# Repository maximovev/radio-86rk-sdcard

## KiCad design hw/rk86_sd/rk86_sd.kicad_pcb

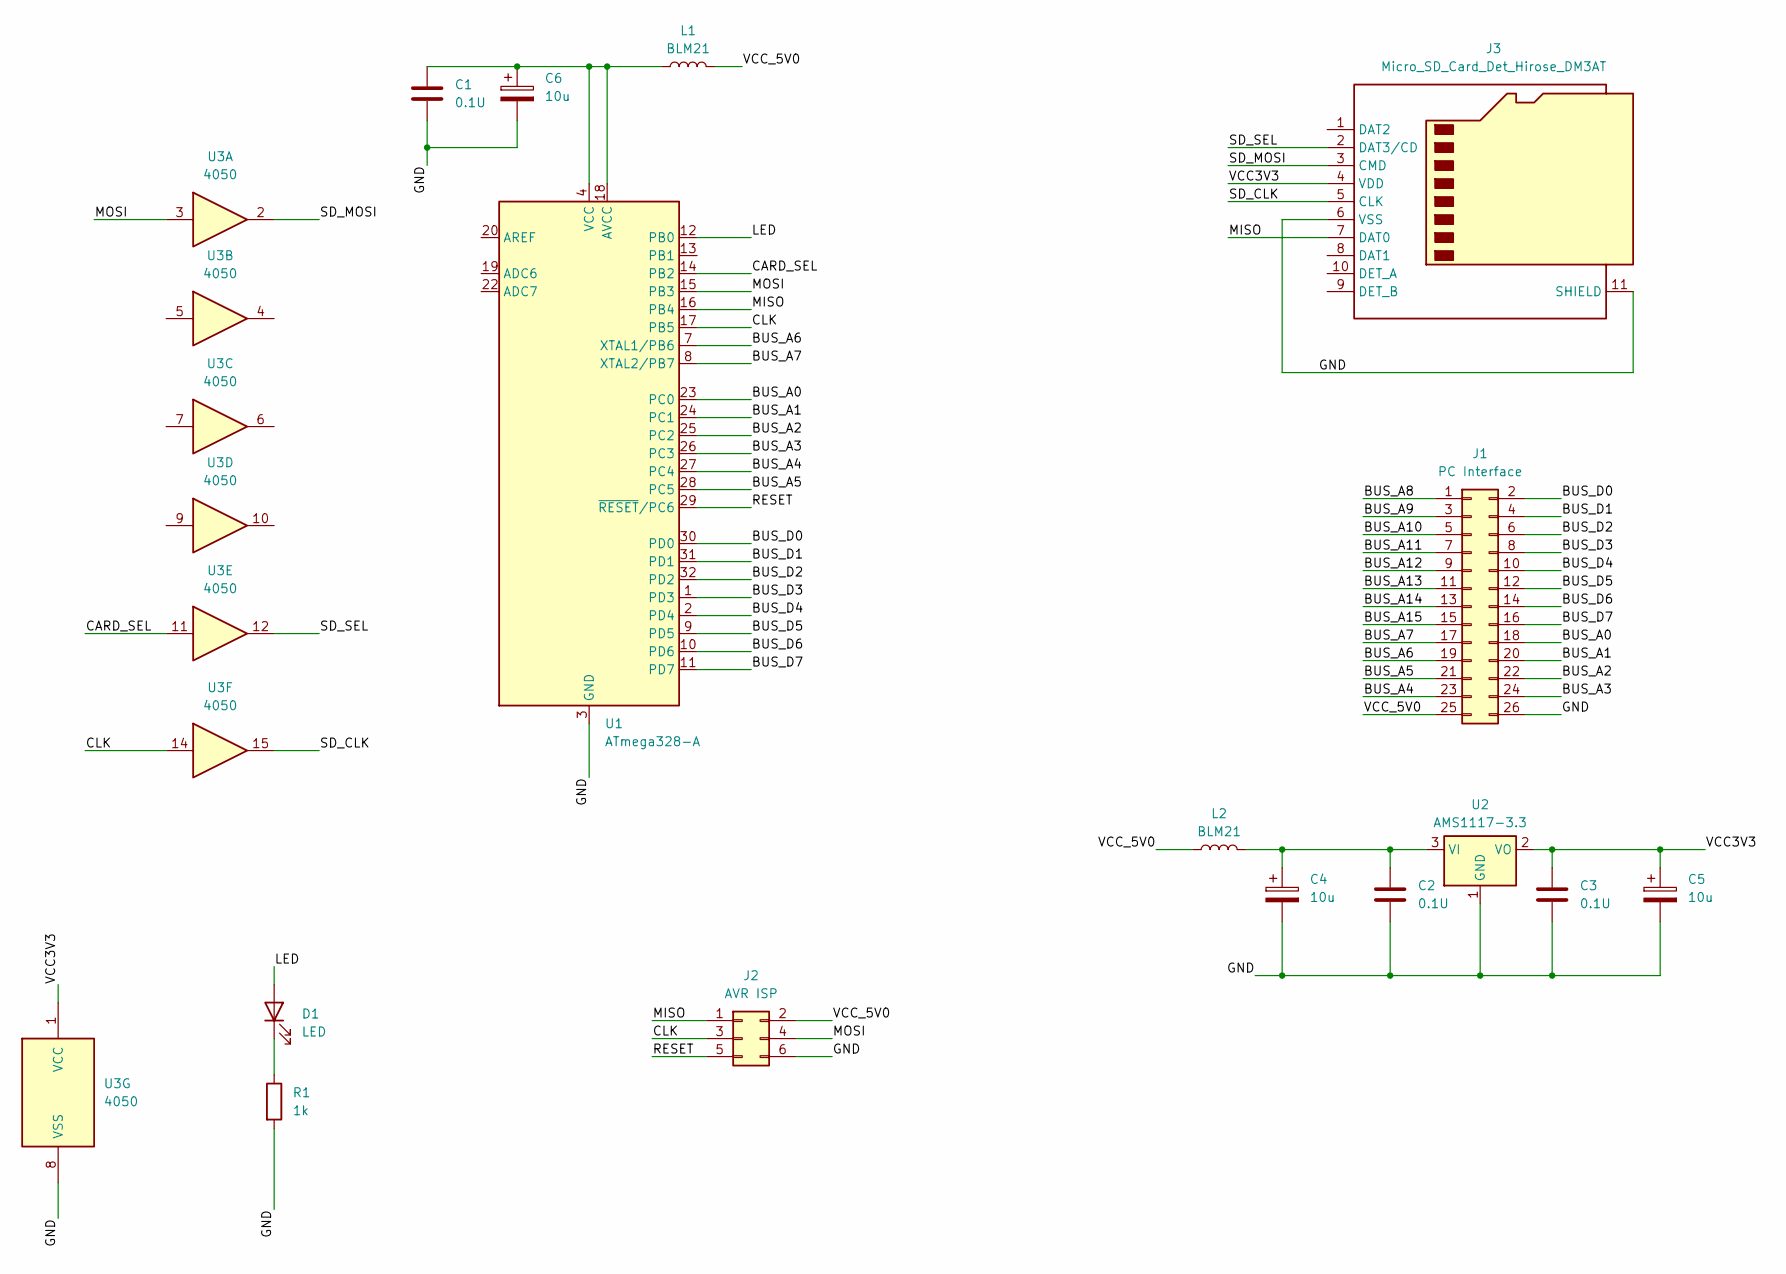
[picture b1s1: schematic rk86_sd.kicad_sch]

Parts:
C1, C2, C3: 0.1U; C_0805_2012Metric_Pad1.18x1.45mm_HandSolder
C4, C5, C6: 10u; CP_EIA-3528-21_Kemet-B_Pad1.50x2.35mm_HandSolder
D1: LED; LED_0805_2012Metric_Pad1.15x1.40mm_HandSolder
J1: PC Interface; IDC-Header_2x13_P2.54mm_Vertical
J2: AVR ISP; PinHeader_2x03_P2.54mm_Vertical
J3: Micro_SD_Card_Det_Hirose_DM3AT; microSD_HC_Hirose_DM3BT-DSF-PEJS
L1, L2: BLM21; L_0805_2012Metric_Pad1.15x1.40mm_HandSolder
R1: 1k; R_0805_2012Metric_Pad1.20x1.40mm_HandSolder
U1: ATmega328-A; TQFP-32_7x7mm_P0.8mm
U2: AMS1117-3.3; SOT-223-3_TabPin2
U3: 4050; SOIC-16_3.9x9.9mm_P1.27mm

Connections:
/BUS_A0: J1.18, U1.23 (PC0)
/BUS_A1: J1.20, U1.24 (PC1)
/BUS_A2: J1.22, U1.25 (PC2)
/BUS_A3: J1.24, U1.26 (PC3)
/BUS_A4: J1.23, U1.27 (PC4)
/BUS_A5: J1.21, U1.28 (PC5)
/BUS_A6: J1.19, U1.7 (XTAL1/PB6)
/BUS_A7: J1.17, U1.8 (XTAL2/PB7)
/BUS_A8: J1.1
/BUS_A9: J1.3
/BUS_A10: J1.5
/BUS_A11: J1.7
/BUS_A12: J1.9
/BUS_A13: J1.11
/BUS_A14: J1.13
/BUS_A15: J1.15
/BUS_D0: J1.2, U1.30 (PD0)
/BUS_D1: J1.4, U1.31 (PD1)
/BUS_D2: J1.6, U1.32 (PD2)
/BUS_D3: J1.8, U1.1 (PD3)
/BUS_D4: J1.10, U1.2 (PD4)
/BUS_D5: J1.12, U1.9 (PD5)
/BUS_D6: J1.14, U1.10 (PD6)
/BUS_D7: J1.16, U1.11 (PD7)
/CARD_SEL: U1.14 (PB2), U3.11
/CLK: J2.3, U1.17 (PB5), U3.14
/GND: C1.2, C2.2, C3.2, C4.2, C5.2, C6.2, J1.26, J2.6, J3.6 (VSS), J3.11 (SHIELD), R1.2, U1.3 (GND), U1.5 (GND), U1.21 (GND), U2.1 (GND), U3.8 (VSS)
/LED: D1.2 (A), U1.12 (PB0)
/MISO: J2.1, J3.7 (DAT0), U1.16 (PB4)
/MOSI: J2.4, U1.15 (PB3), U3.3
/RESET: J2.5, U1.29 (~RESET/PC6)
/SD_CLK: J3.5 (CLK), U3.15
/SD_MOSI: J3.3 (CMD), U3.2
/SD_SEL: J3.2 (DAT3/CD), U3.12
/VCC3V3: C3.1, C5.1, J3.4 (VDD), U2.2 (VO), U3.1 (VCC)
/VCC_5V0: J1.25, J2.2, L1.2, L2.1
unnamed: D1.1 (K), R1.1
unnamed: C1.1, C6.1, L1.1, U1.4 (VCC), U1.6 (VCC), U1.18 (AVCC)
unnamed: C2.1, C4.1, L2.2, U2.3 (VI)

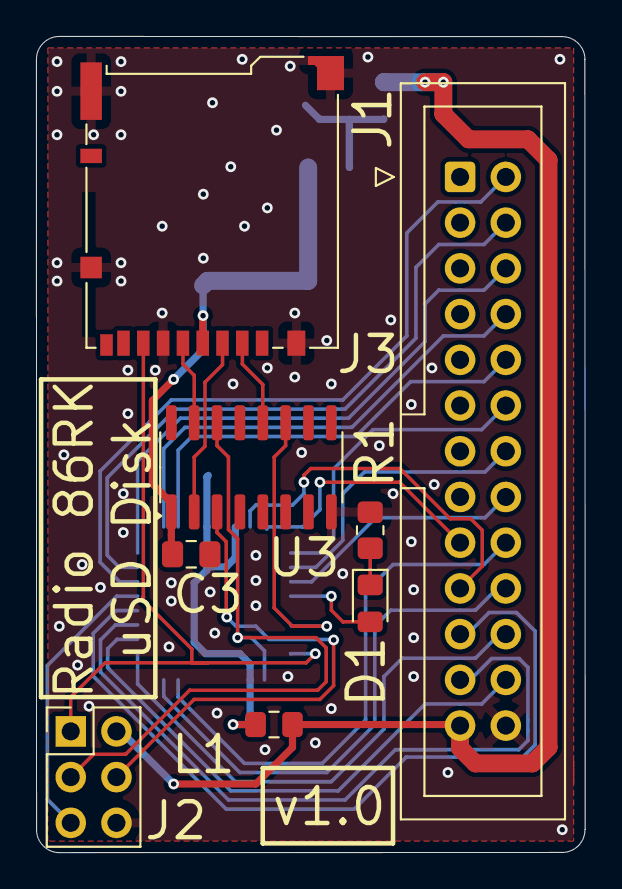
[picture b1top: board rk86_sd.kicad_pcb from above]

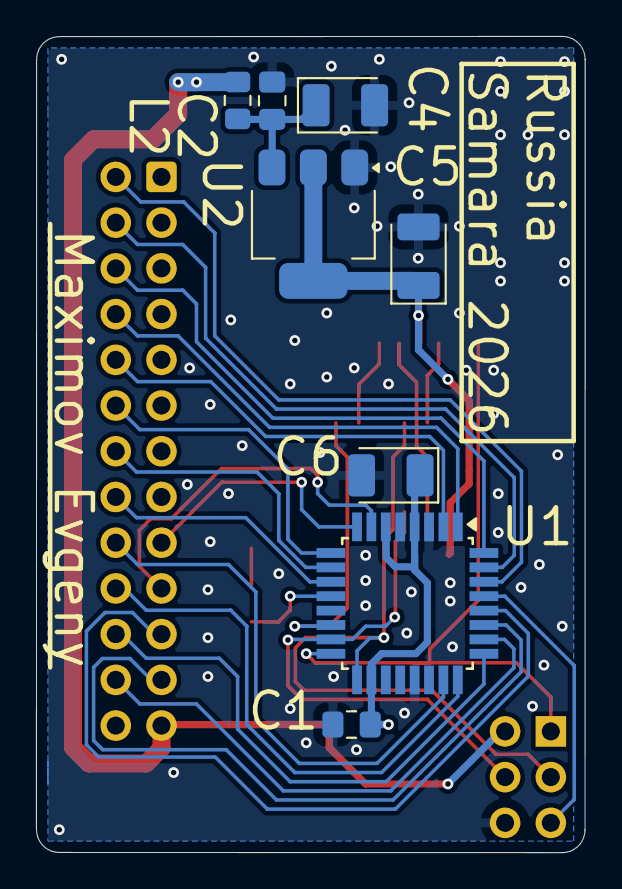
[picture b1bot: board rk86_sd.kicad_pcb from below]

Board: 2 copper layers, 30.5 x 45.3 mm, 16 parts (8 on the bottom side), 31 nets.

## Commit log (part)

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2026-04-23 Recovered v2.0 of the PCB
